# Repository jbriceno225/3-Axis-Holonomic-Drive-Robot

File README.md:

# KiwiDrive — Three-Wheel Holonomic Robot

A work-in-progress mobile robotics platform built around three omni wheels, an ESP32 controller, quadrature encoders, custom mechanical design, and a ROS 2 workspace.

> **Project status:** active development. The repository contains the current design and software artifacts; physical-system validation is in progress.

## What is in this repository

- **Mechanical design:** Fusion 360 assemblies, STEP exports, and printable STL parts in [`CAD/`](CAD/).
- **Electronics:** KiCad Rev A project files, fabrication outputs, and a purchasing BOM in [`PCB/`](PCB/).
- **Embedded control:** ESP32 firmware for three motor channels, encoder feedback, PID velocity control, Bluetooth gamepad control, and a serial-command safety timeout in [`ESP32_Code/`](ESP32_Code/).
- **ROS 2 integration:** Robot-description files, RViz configuration, serial-command bridge code, and vendor dependencies in [`src/`](src/).

## System overview

```text
Operator / ROS 2 command
          |
          v
  Raspberry Pi + ROS 2 workspace
          |
          v
       Serial interface
          |
          v
ESP32 -> motor drivers -> three DC motors
  ^                              |
  +--------- quadrature encoders-+
```

The three-wheel omni-wheel layout is intended to support holonomic translation and rotation. Current software includes manual control and the foundations for command bridging, robot description, and odometry work.

## Repository layout

```text
CAD/          Fusion 360 sources, STEP exports, and 3D-printable parts
PCB/          Rev A KiCad design, Gerbers, drill files, and BOM
ESP32_Code/   ESP32 firmware
src/          ROS 2 description, serial bridge, and third-party dependencies
patches/      Local patch overlays for selected dependencies
```

## Current development focus

- Integrating ESP32 motor control, encoder feedback, and safety behavior.
- Building out the ROS 2 robot description and serial bridge.
- Validating wheel kinematics, odometry, and hardware behavior through staged testing.
- Documenting CAD, PCB, firmware, and ROS 2 interfaces as the system matures.

## Safety

Test with the drive wheels raised during initial firmware and controller checks. Use an accessible physical power cutoff for floor testing; a software timeout is not a substitute for a physical emergency stop.

## Tools

**Mechanical:** Fusion 360, STEP, STL, 3D printing  
**Electronics:** KiCad, ESP32, TB6612FNG motor drivers, quadrature encoders  
**Software:** C/C++, Python, ROS 2, PID control, serial communication

## License

This project is licensed under the [MIT License](LICENSE).

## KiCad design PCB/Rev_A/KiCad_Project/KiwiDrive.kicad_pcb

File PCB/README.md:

# PCB

KiCad source and fabrication outputs for the Rev A KiwiDrive
module-carrier/control board.

## Layout

- `Rev_A/KiCad_Project/`: schematic, PCB layout, project settings, and local
  footprint-library mapping.
- `Rev_A/Fabrication/Gerbers/`: copper, mask, paste, silkscreen, edge cuts, and
  job file.
- `Rev_A/Fabrication/Drill_Files/`: plated and non-plated drill data.
- `Rev_A/Fabrication/BOM/`: purchasing BOM exported from the project.
- `Libraries/Footprints/`: project-specific footprints for the ESP32 DevKit,
  TB6612FNG carrier, motor/encoder connector, battery input, test point, and
  logo.

Rev A carries an ESP32 DevKit V1, three TB6612FNG driver modules, a
R-78E5.0-1.0 converter module, and motor/encoder and power interconnects. See
[`docs/hardware.md`](../docs/hardware.md) for firmware pin mapping and the
Rev B direction.

## Review before fabrication

The presence of Gerbers is not fabrication approval. Open the KiCad source and
run electrical and design-rule checks. Then verify:

- board outline, layer count, drill tolerances, and manufacturer rules;
- footprint dimensions, pin 1/orientation, connector gender, and keying;
- battery polarity, voltage ratings, motor stall current, copper width,
  grounding, return paths, clearance, and thermal margin;
- converter and driver module part numbers against the actual purchased parts;
- schematic-to-firmware GPIO continuity;
- BOM completeness and substitutions;
- Gerber/drill alignment in an independent viewer.

Initial power-up must use a current-limited supply with motors disconnected.
Rev A does not provide the planned Rev B master switch, branch fuses,
protection/passives, status indicators, or integrated drivers; add external
protection and a physical emergency cutoff during development.

When releasing revised fabrication files, keep editable source and outputs in
the same revision directory and record the KiCad version used. Do not modify
third-party footprint headers or licensing without attribution.

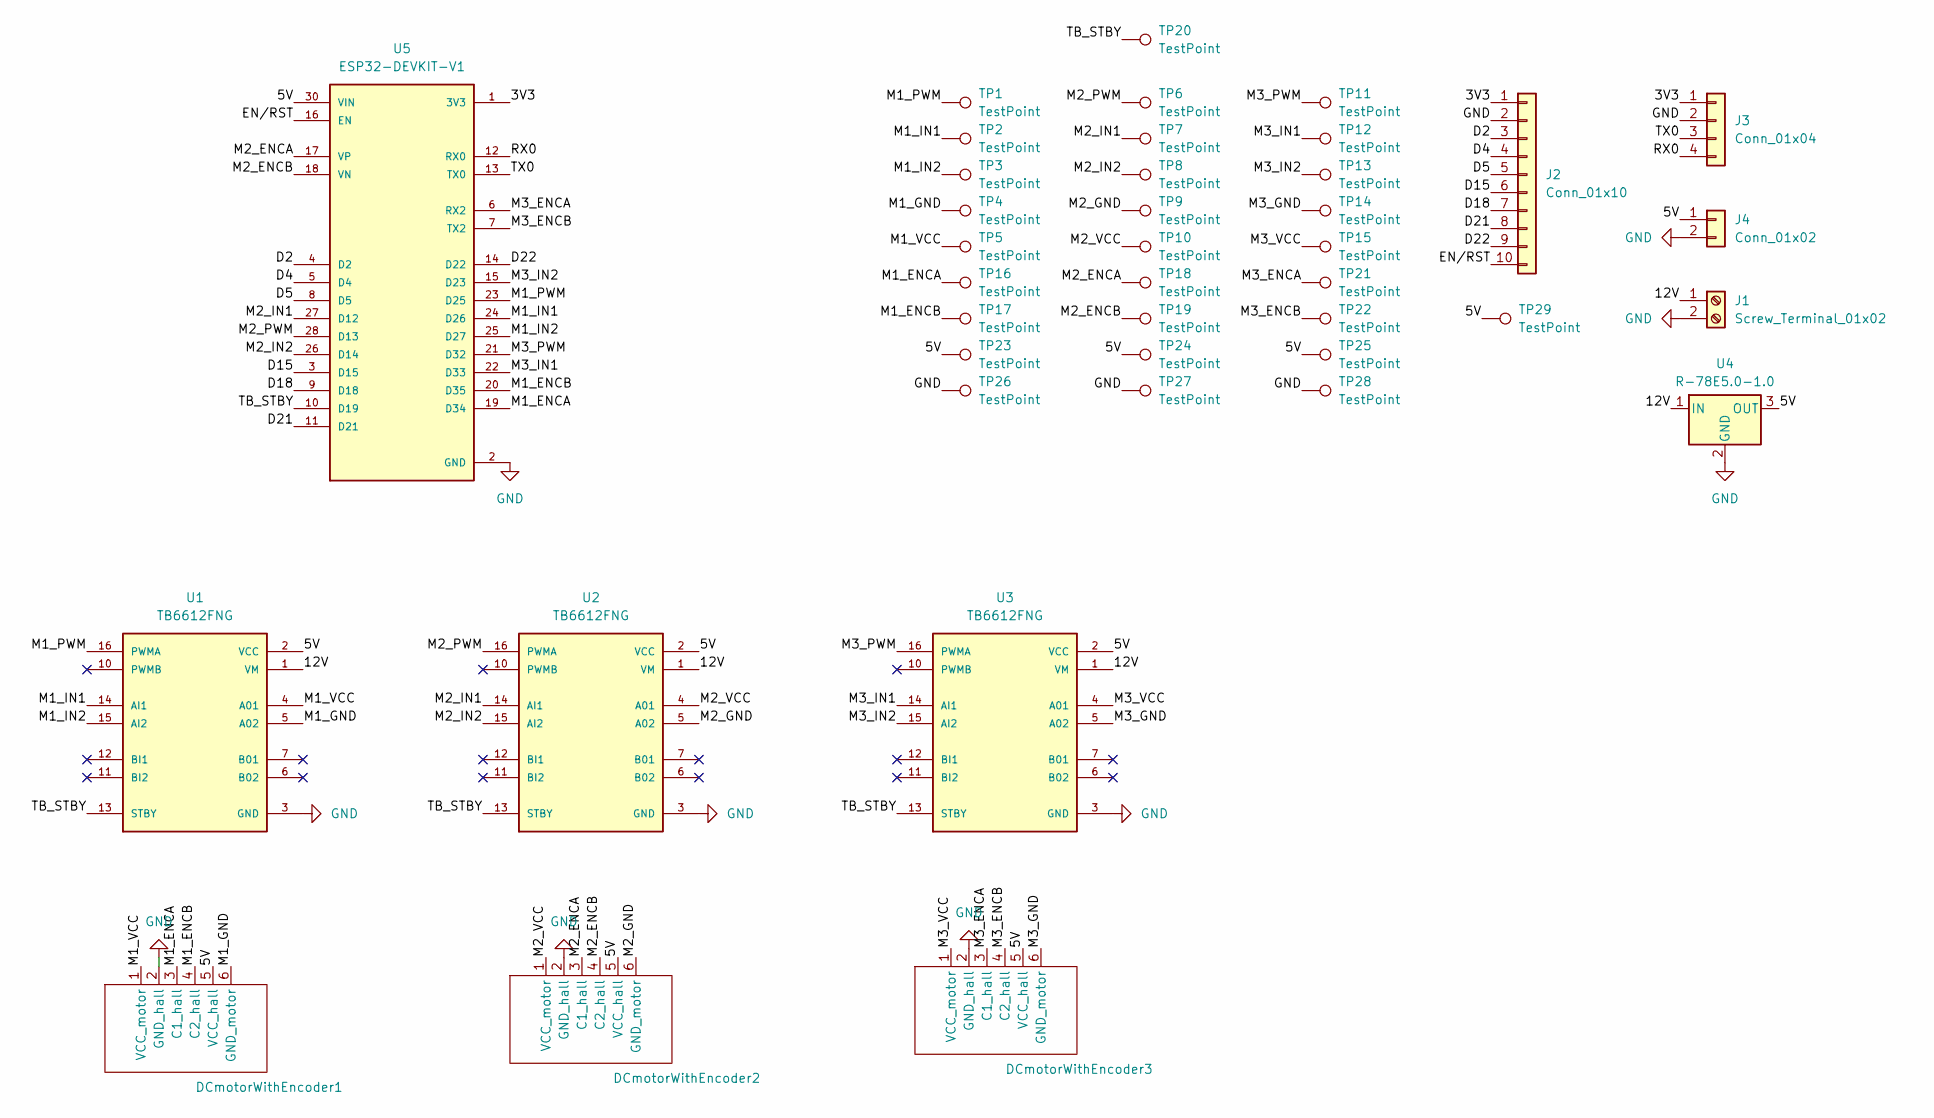
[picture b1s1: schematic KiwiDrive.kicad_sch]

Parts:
DCmotorWithEncoder1, DCmotorWithEncoder2, DCmotorWithEncoder3: 25GA_Motor_Encoder_6Pin
J1: Screw_Terminal_01x02; AMASS_XT30PW-F_1x02_P2.50mm_Horizontal
J2: Conn_01x10; PinHeader_1x10_P2.54mm_Vertical
J3: Conn_01x04; PinHeader_1x04_P2.54mm_Vertical
J4: Conn_01x02; PinHeader_1x02_P2.54mm_Vertical
TP1, TP2, TP3, TP4, TP5, TP6, TP7, TP8, TP9, TP10, TP11, TP12, TP13, TP14, TP15, TP16, TP17, TP18, TP19, TP20, TP21, TP22, TP23, TP24, TP25, TP26, TP27, TP28, TP29: TestPoint; TestPoint_Pad_1.0x1.0mm
U1, U2, U3: TB6612FNG
U4: R-78E5.0-1.0; Converter_DCDC_RECOM_R-78E-0.5_THT
U5: ESP32-DEVKIT-V1; MODULE_ESP32_DEVKIT_V1; PARTREV N/A

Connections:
/3V3: J2.1, J3.1, U5.1 (3V3)
/5V: DCmotorWithEncoder1.5 (VCC_hall), DCmotorWithEncoder2.5 (VCC_hall), DCmotorWithEncoder3.5 (VCC_hall), J4.1, TP23.1 (1_1), TP24.1 (1_1), TP25.1 (1_1), TP29.1 (1_1), U1.2 (VCC), U2.2 (VCC), U3.2 (VCC), U4.3 (OUT), U5.30 (VIN)
/12V: J1.1, U1.1 (VM), U2.1 (VM), U3.1 (VM), U4.1 (IN)
/D2: J2.3, U5.4 (D2)
/D4: J2.4, U5.5 (D4)
/D5: J2.5, U5.8 (D5)
/D15: J2.6, U5.3 (D15)
/D18: J2.7, U5.9 (D18)
/D21: J2.8, U5.11 (D21)
/D22: J2.9, U5.14 (D22)
/EN/RST: J2.10, U5.16 (EN)
/M1_ENCA: DCmotorWithEncoder1.3 (C1_hall), TP16.1 (1_1), U5.19 (D34)
/M1_ENCB: DCmotorWithEncoder1.4 (C2_hall), TP17.1 (1_1), U5.20 (D35)
/M1_GND: DCmotorWithEncoder1.6 (GND_motor), TP4.1 (1_1), U1.5 (A02)
/M1_IN1: TP2.1 (1_1), U1.14 (AI1), U5.24 (D26)
/M1_IN2: TP3.1 (1_1), U1.15 (AI2), U5.25 (D27)
/M1_PWM: TP1.1 (1_1), U1.16 (PWMA), U5.23 (D25)
/M1_VCC: DCmotorWithEncoder1.1 (VCC_motor), TP5.1 (1_1), U1.4 (A01)
/M2_ENCA: DCmotorWithEncoder2.3 (C1_hall), TP18.1 (1_1), U5.17 (VP)
/M2_ENCB: DCmotorWithEncoder2.4 (C2_hall), TP19.1 (1_1), U5.18 (VN)
/M2_GND: DCmotorWithEncoder2.6 (GND_motor), TP9.1 (1_1), U2.5 (A02)
/M2_IN1: TP7.1 (1_1), U2.14 (AI1), U5.27 (D12)
/M2_IN2: TP8.1 (1_1), U2.15 (AI2), U5.26 (D14)
/M2_PWM: TP6.1 (1_1), U2.16 (PWMA), U5.28 (D13)
/M2_VCC: DCmotorWithEncoder2.1 (VCC_motor), TP10.1 (1_1), U2.4 (A01)
/M3_ENCA: DCmotorWithEncoder3.3 (C1_hall), TP21.1 (1_1), U5.6 (RX2)
/M3_ENCB: DCmotorWithEncoder3.4 (C2_hall), TP22.1 (1_1), U5.7 (TX2)
/M3_GND: DCmotorWithEncoder3.6 (GND_motor), TP14.1 (1_1), U3.5 (A02)
/M3_IN1: TP12.1 (1_1), U3.14 (AI1), U5.22 (D33)
/M3_IN2: TP13.1 (1_1), U3.15 (AI2), U5.15 (D23)
/M3_PWM: TP11.1 (1_1), U3.16 (PWMA), U5.21 (D32)
/M3_VCC: DCmotorWithEncoder3.1 (VCC_motor), TP15.1 (1_1), U3.4 (A01)
/RX0: J3.4, U5.12 (RX0)
/TB_STBY: TP20.1 (1_1), U1.13 (STBY), U2.13 (STBY), U3.13 (STBY), U5.10 (D19)
/TX0: J3.3, U5.13 (TX0)
GND: DCmotorWithEncoder1.2 (GND_hall), DCmotorWithEncoder2.2 (GND_hall), DCmotorWithEncoder3.2 (GND_hall), J1.2, J2.2, J3.2, J4.2, TP26.1 (1_1), TP27.1 (1_1), TP28.1 (1_1), U1.3 (GND), U1.8 (GND), U1.9 (GND), U2.3 (GND), U2.8 (GND), U2.9 (GND), U3.3 (GND), U3.8 (GND), U3.9 (GND), U4.2 (GND), U5.2 (GND), U5.29 (GND)

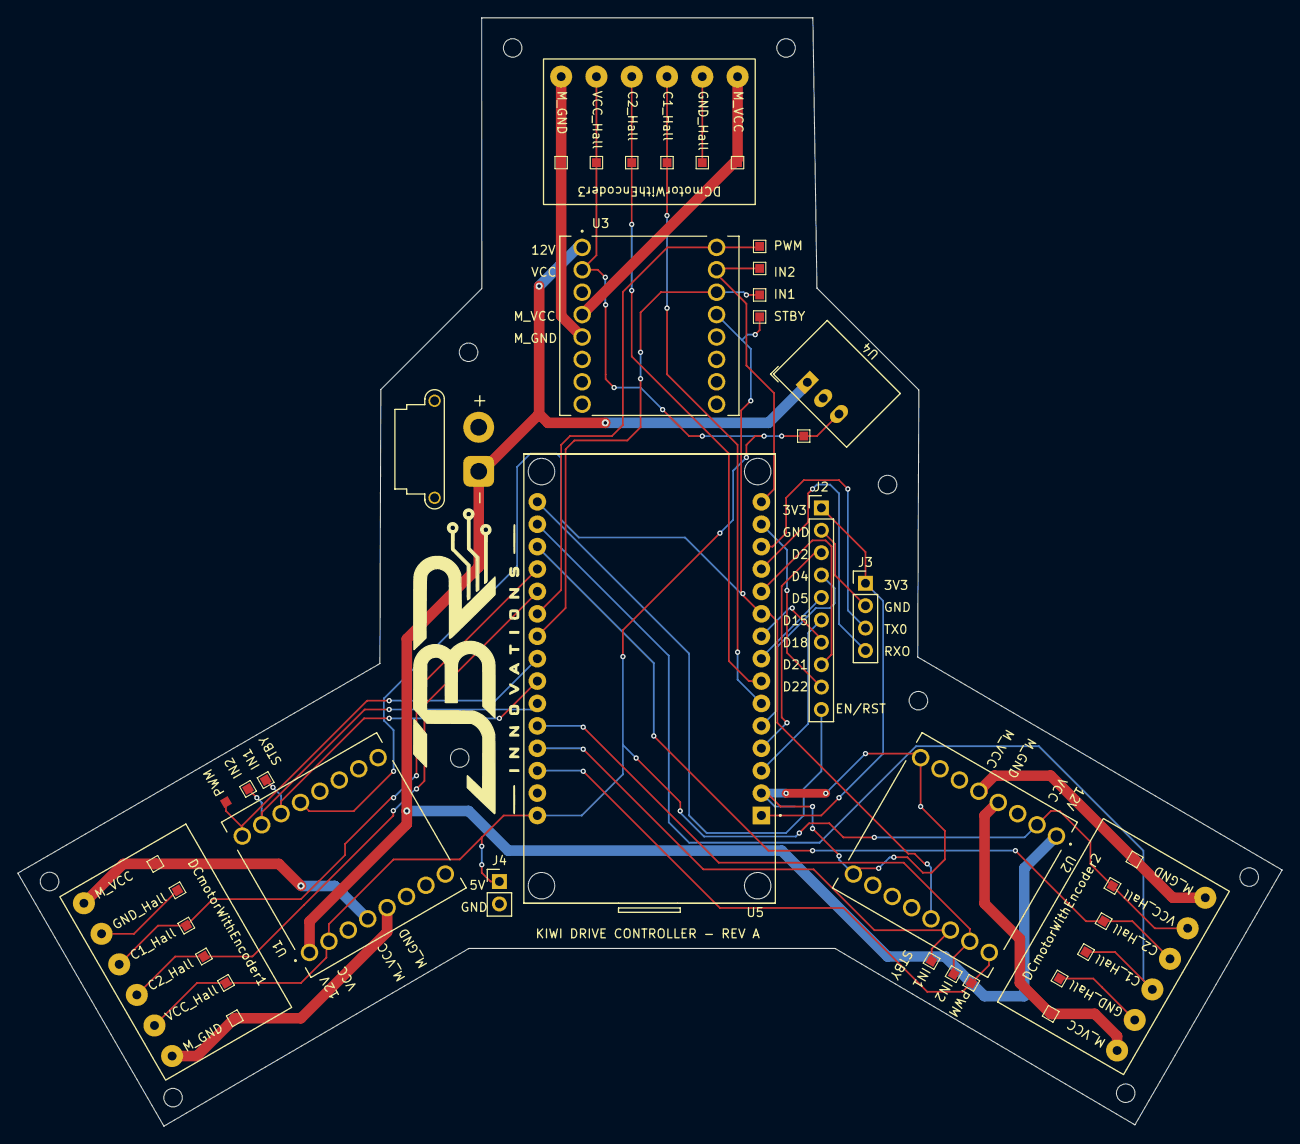
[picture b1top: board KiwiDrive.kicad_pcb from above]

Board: 2 copper layers, 143.3 x 125.6 mm, 41 parts (0 on the bottom side), 36 nets.

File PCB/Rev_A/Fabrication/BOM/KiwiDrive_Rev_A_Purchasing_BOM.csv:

"Reference","Qty","Value","DNP","Exclude from BOM","Exclude from Board","Footprint","Datasheet"
"DCmotorWithEncoder1,DCmotorWithEncoder2,DCmotorWithEncoder3","3","","","","","25GA_Motor_Encoder:25GA_Motor_Encoder_6Pin",""
"J1","1","Screw_Terminal_01x02","","","","Connector_AMASS:AMASS_XT30PW-F_1x02_P2.50mm_Horizontal",""
"J2","1","Conn_01x10","","","","Connector_PinHeader_2.54mm:PinHeader_1x10_P2.54mm_Vertical",""
"J3","1","Conn_01x04","","","","Connector_PinHeader_2.54mm:PinHeader_1x04_P2.54mm_Vertical",""
"J4","1","Conn_01x02","","","","Connector_PinHeader_2.54mm:PinHeader_1x02_P2.54mm_Vertical",""
"TP1,TP2,TP3,TP4,TP5,TP6,TP7,TP8,TP9,TP10,TP11,TP12,TP13,TP14,TP15,TP16,TP17,TP18,TP19,TP20,TP21,TP22,TP23,TP24,TP25,TP26,TP27,TP28,TP29","29","TestPoint","","","","TestPoint:TestPoint_Pad_1.0x1.0mm",""
"U1,U2,U3","3","TB6612FNG","","","","TB6612FNG:TB6612FNG",""
"U4","1","R-78E5.0-1.0","","","","Converter_DCDC:Converter_DCDC_RECOM_R-78E-0.5_THT","https://www.recom-power.com/pdf/Innoline/R-78Exx-1.0.pdf"
"U5","1","ESP32-DEVKIT-V1","","","","ESP32:MODULE_ESP32_DEVKIT_V1",""

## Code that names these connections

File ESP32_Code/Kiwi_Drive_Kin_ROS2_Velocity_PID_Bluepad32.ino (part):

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const uint8_t STBY = 19;

// ---------------- Motor 1 ----------------
const uint8_t M1_PWM = 25;
const uint8_t M1_IN1 = 26;
const uint8_t M1_IN2 = 27;
    //------------- Motor 1 Encoder --------
const uint8_t M1_ENCA = 34;
const uint8_t M1_ENCB = 35;

// ---------------- Motor 2 ----------------
const uint8_t M2_PWM = 13;
const uint8_t M2_IN1 = 12;
const uint8_t M2_IN2 = 14;

    //------------- Motor 1 Encoder --------
    // VP = GPIO36
    // VN = GPIO39
const uint8_t M2_ENCA = 36;
const uint8_t M2_ENCB = 39;

// ---------------- Motor 3 ----------------

const uint8_t M3_PWM = 32;
const uint8_t M3_IN1 = 33;
const uint8_t M3_IN2 = 23;

    //------------- Motor 1 Encoder --------
    // RX2 = GPIO16
    // TX2 = GPIO17
const uint8_t M3_ENCA = 16;
const uint8_t M3_ENCB = 17;



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    PWM_RESOLUTION_BITS
  );

  ledcAttachPin(M1_PWM, M1_PWM_CHANNEL);
  ledcAttachPin(M2_PWM, M2_PWM_CHANNEL);
  ledcAttachPin(M3_PWM, M3_PWM_CHANNEL);

  bool motor1Attached = true;
  bool motor2Attached = true;
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  pinMode(STBY, OUTPUT);
  disableMotorDrivers();

  pinMode(M1_IN1, OUTPUT);
  pinMode(M1_IN2, OUTPUT);

  pinMode(M2_IN1, OUTPUT);
  pinMode(M2_IN2, OUTPUT);

  pinMode(M3_IN1, OUTPUT);
  pinMode(M3_IN2, OUTPUT);

  /*
    GPIO34, GPIO35, GPIO36, and GPIO39 do not have
    internal pull-up or pull-down resistors.
  */
  pinMode(M1_ENCA, INPUT);
  pinMode(M1_ENCB, INPUT);

  pinMode(M2_ENCA, INPUT);
  pinMode(M2_ENCB, INPUT);

  pinMode(M3_ENCA, INPUT);
  pinMode(M3_ENCB, INPUT);

  previousEncoderState[0] =
    (digitalRead(M1_ENCA) << 1) |
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    digitalRead(M3_ENCB);

  attachInterrupt(
    digitalPinToInterrupt(M1_ENCA),
    motor1EncoderISR,
    CHANGE
  );

  attachInterrupt(
    digitalPinToInterrupt(M1_ENCB),
    motor1EncoderISR,
    CHANGE
  );

  attachInterrupt(
    digitalPinToInterrupt(M2_ENCA),
    motor2EncoderISR,
    CHANGE
  );

  attachInterrupt(
    digitalPinToInterrupt(M2_ENCB),
    motor2EncoderISR,
    CHANGE
  );

  attachInterrupt(
    digitalPinToInterrupt(M3_ENCA),
    motor3EncoderISR,
    CHANGE
  );

  attachInterrupt(
    digitalPinToInterrupt(M3_ENCB),
    motor3EncoderISR,
    CHANGE
  );
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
